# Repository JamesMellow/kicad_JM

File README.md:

# kicad_JM
Collection od different Kicad files including some:
-selfmade footprints
-projects
-gerber files

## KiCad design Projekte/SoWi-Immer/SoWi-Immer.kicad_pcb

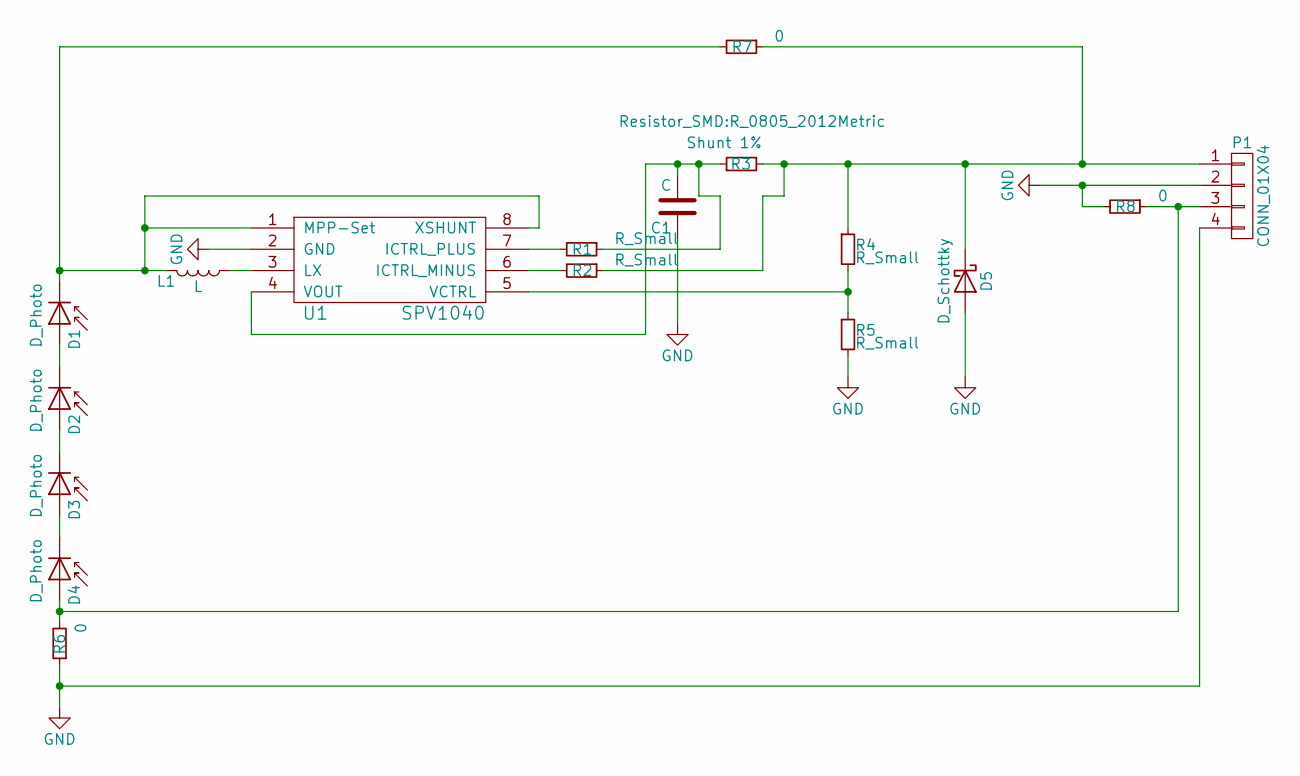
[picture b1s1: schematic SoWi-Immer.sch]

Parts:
C1: C; C_1206_3216Metric
D1, D2, D3, D4: D_Photo; KXOB22-12X1F
D5: D_Schottky; D_0805
L1: L; R_0815_2038Metric
P1: CONN_01X04; PinHeader_1x04_P1.27mm_Vertical
R1, R2, R4, R5: R_Small; R_0805_2012Metric
R3: Shunt 1%; R_0805_2012Metric
R6, R7, R8: 0; R_0805_2012Metric
U1: SPV1040; TSSOP-8_4.4x3mm_P0.65mm

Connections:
GND: C1.1, D5.2 (A), P1.2, P1.4, R5.2, R6.1, R8.2, U1.2 (GND)
unnamed: C1.2, R1.1, R3.1, U1.4 (VOUT)
unnamed: D1.1 (K), L1.2, R7.2, U1.1 (MPP-Set), U1.8 (XSHUNT)
unnamed: D1.2 (A), D2.1 (K)
unnamed: D2.2 (A), D3.1 (K)
unnamed: D3.2 (A), D4.1 (K)
unnamed: D4.2 (A), P1.3, R6.2, R8.1
unnamed: D5.1 (K), P1.1, R2.1, R3.2, R4.1, R7.1
unnamed: L1.1, U1.3 (LX)
unnamed: R1.2, U1.7 (ICTRL_PLUS)
unnamed: R2.2, U1.6 (ICTRL_MINUS)
unnamed: R4.2, R5.1, U1.5 (VCTRL)

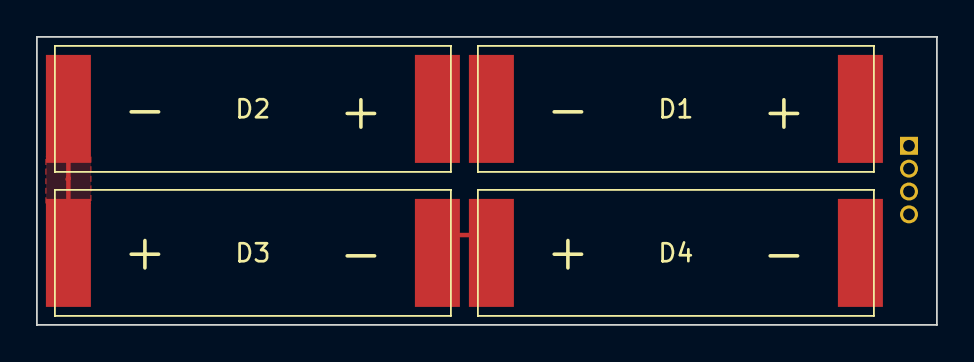
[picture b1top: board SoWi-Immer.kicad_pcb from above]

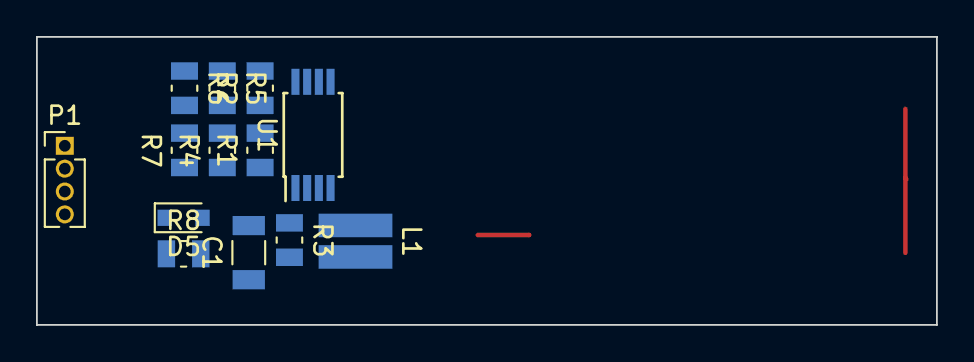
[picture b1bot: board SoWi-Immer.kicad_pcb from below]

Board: 2 copper layers, 50.0 x 16.0 mm, 17 parts (13 on the bottom side), 12 nets.

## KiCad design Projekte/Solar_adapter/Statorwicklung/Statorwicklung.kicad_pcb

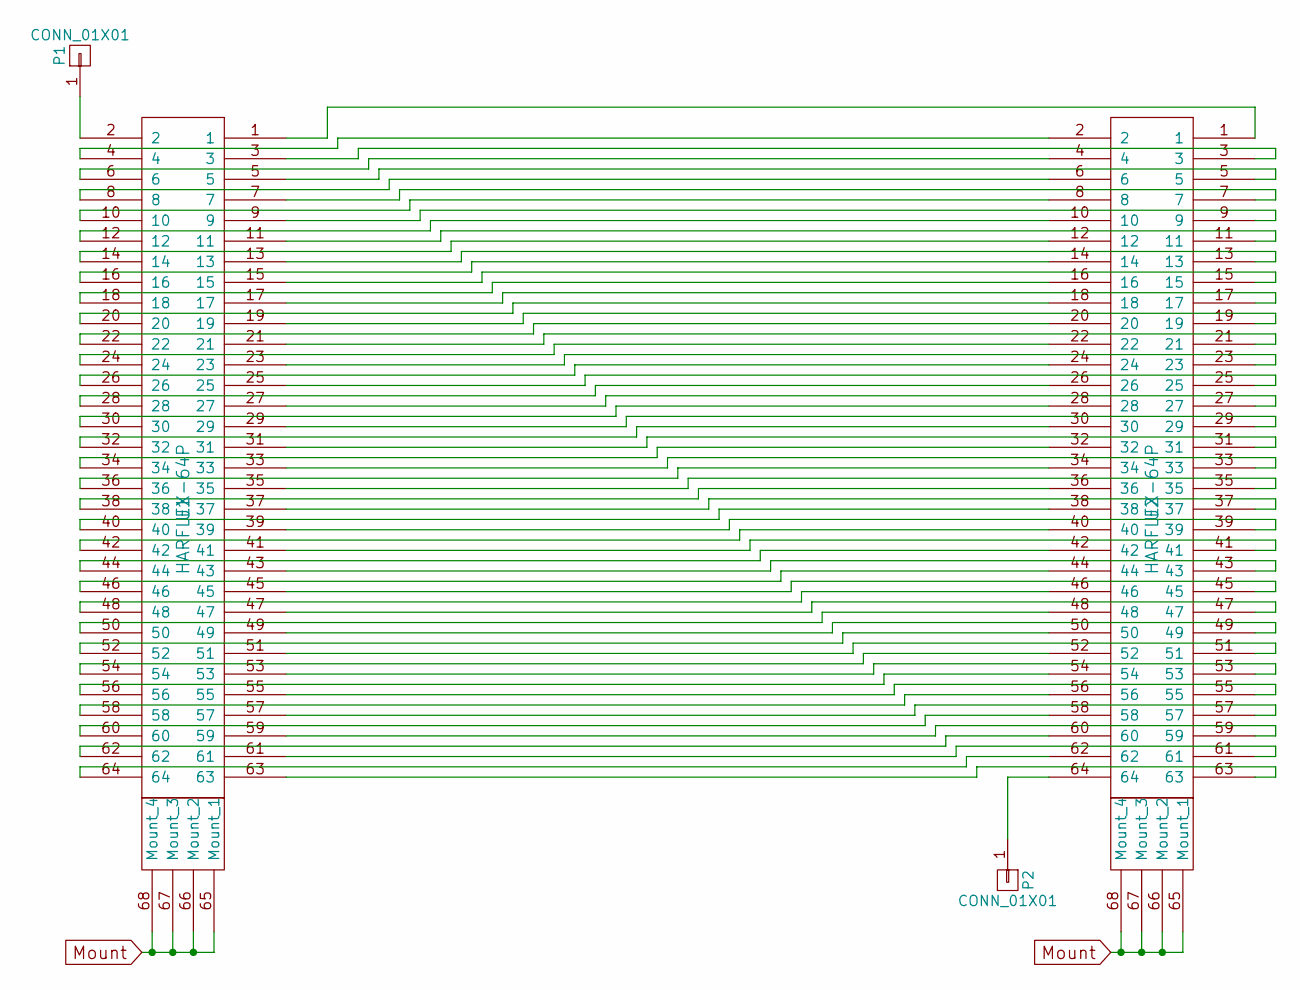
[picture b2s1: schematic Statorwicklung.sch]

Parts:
P1, P2: CONN_01X01; 1pin
U1, U2: HARFLEX-64P; Harting_64p_Stiftleiste

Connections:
Mount: U1.65 (Mount_1), U1.66 (Mount_2), U1.67 (Mount_3), U1.68 (Mount_4), U2.65 (Mount_1), U2.66 (Mount_2), U2.67 (Mount_3), U2.68 (Mount_4)
unnamed: P1.1, U1.2
unnamed: P2.1, U2.64
unnamed: U1.1, U2.1
unnamed: U1.3, U2.3
unnamed: U1.4, U2.2
unnamed: U1.5, U2.5
unnamed: U1.6, U2.4
unnamed: U1.7, U2.7
unnamed: U1.8, U2.6
unnamed: U1.9, U2.9
unnamed: U1.10, U2.8
unnamed: U1.11, U2.11
unnamed: U1.12, U2.10
unnamed: U1.13, U2.13
unnamed: U1.14, U2.12
unnamed: U1.15, U2.15
unnamed: U1.16, U2.14
unnamed: U1.17, U2.17
unnamed: U1.18, U2.16
unnamed: U1.19, U2.19
unnamed: U1.20, U2.18
unnamed: U1.21, U2.21
unnamed: U1.22, U2.20
unnamed: U1.23, U2.23
unnamed: U1.24, U2.22
unnamed: U1.25, U2.25
unnamed: U1.26, U2.24
unnamed: U1.27, U2.27
unnamed: U1.28, U2.26
unnamed: U1.29, U2.29
unnamed: U1.30, U2.28
unnamed: U1.31, U2.31
unnamed: U1.32, U2.30
unnamed: U1.33, U2.33
unnamed: U1.34, U2.32
unnamed: U1.35, U2.35
unnamed: U1.36, U2.34
unnamed: U1.37, U2.37
unnamed: U1.38, U2.36
unnamed: U1.39, U2.39
unnamed: U1.40, U2.38
unnamed: U1.41, U2.41
unnamed: U1.42, U2.40
unnamed: U1.43, U2.43
unnamed: U1.44, U2.42
unnamed: U1.45, U2.45
unnamed: U1.46, U2.44
unnamed: U1.47, U2.47
unnamed: U1.48, U2.46
unnamed: U1.49, U2.49
unnamed: U1.50, U2.48
unnamed: U1.51, U2.51
unnamed: U1.52, U2.50
unnamed: U1.53, U2.53
unnamed: U1.54, U2.52
unnamed: U1.55, U2.55
unnamed: U1.56, U2.54
unnamed: U1.57, U2.57
unnamed: U1.58, U2.56
unnamed: U1.59, U2.59
unnamed: U1.60, U2.58
unnamed: U1.61, U2.61
unnamed: U1.62, U2.60
unnamed: U1.63, U2.63
unnamed: U1.64, U2.62

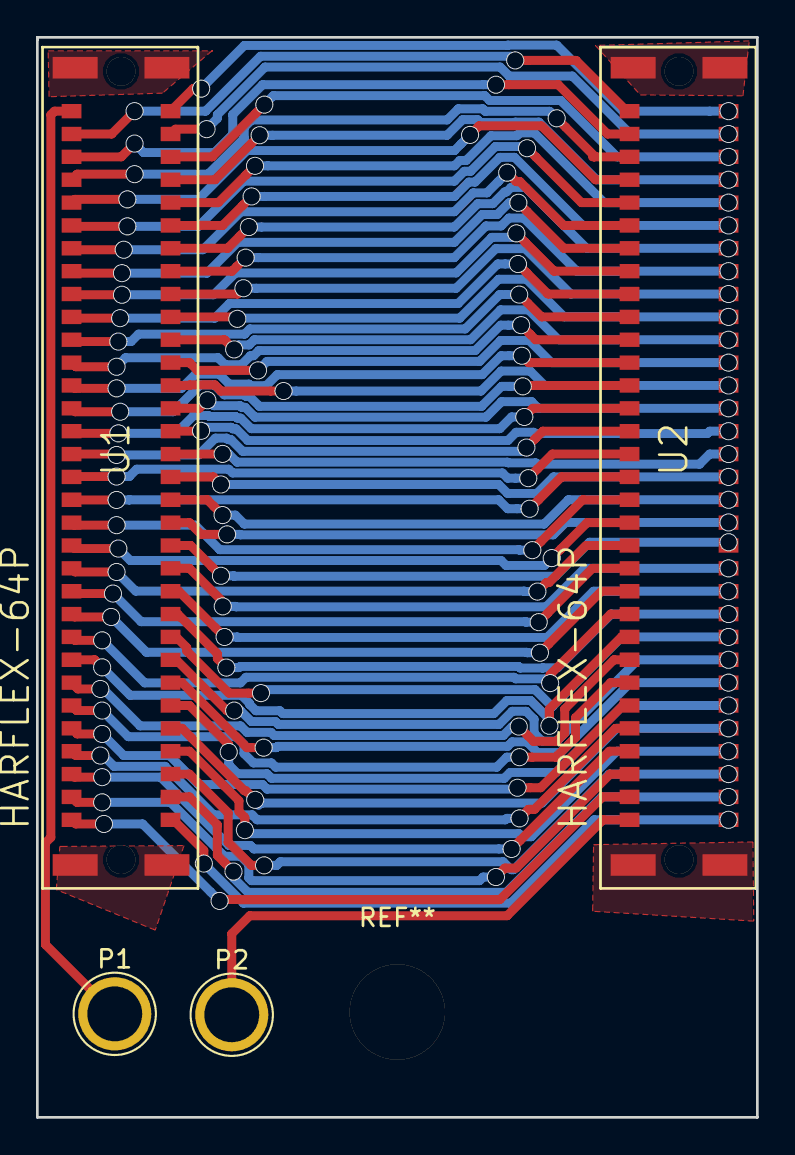
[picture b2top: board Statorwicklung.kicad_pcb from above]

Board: 2 copper layers, 40.0 x 60.0 mm, 4 parts (0 on the bottom side), 66 nets.

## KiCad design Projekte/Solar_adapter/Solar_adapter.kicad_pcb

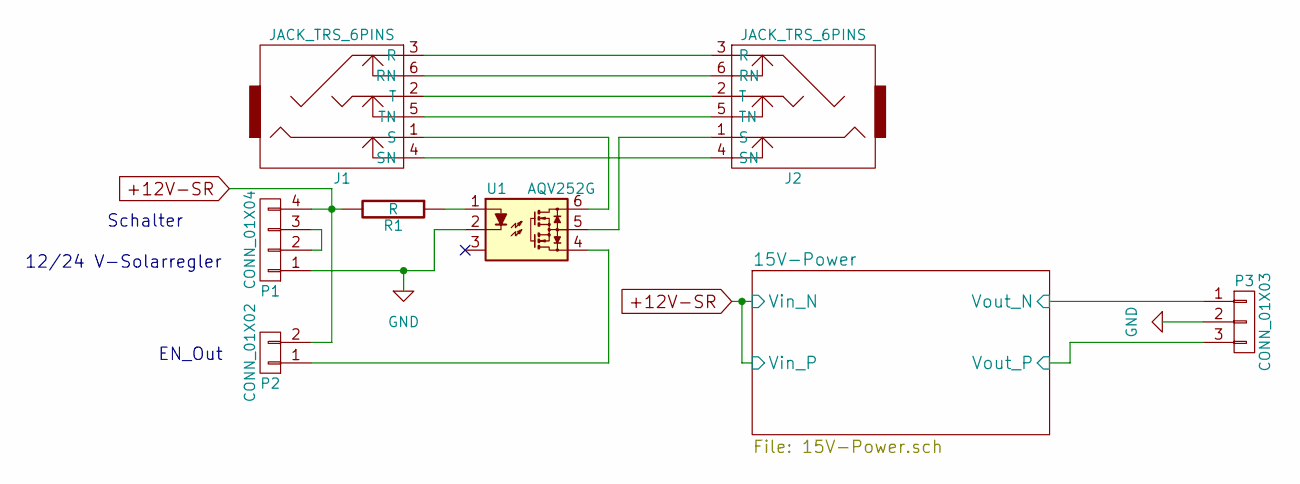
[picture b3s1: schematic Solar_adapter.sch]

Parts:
J1, J2: JACK_TRS_6PINS; RJ12_E
P1: CONN_01X04; WAGO_734_4pin_Straight
P2: CONN_01X02; WAGO_734_2pin_Straight
P3: CONN_01X03; WAGO_734_3pin_Straight
R1: R; R_0805_HandSoldering
U1: AQV252G; DIP-6_W7.62mm

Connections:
+12V-SR: P1.4, P2.2, R1.2; also elsewhere on the board
GND: P1.1, P3.2, U1.2; also elsewhere on the board
unnamed: J1.1 (S), U1.6
unnamed: J1.2 (T), J2.2 (T)
unnamed: J1.3 (R), J2.3 (R)
unnamed: J1.4 (SN), J2.4 (SN)
unnamed: J1.5 (TN), J2.5 (TN)
unnamed: J1.6 (RN), J2.6 (RN)
unnamed: J2.1 (S), U1.5
unnamed: P1.2, P1.3
unnamed: P2.1, U1.4
unnamed: R1.1, U1.1
OUT_N: P3.1; also elsewhere on the board
OUT_P: P3.3; also elsewhere on the board

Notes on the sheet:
Schalter
12/24 V-Solarregler
EN_Out

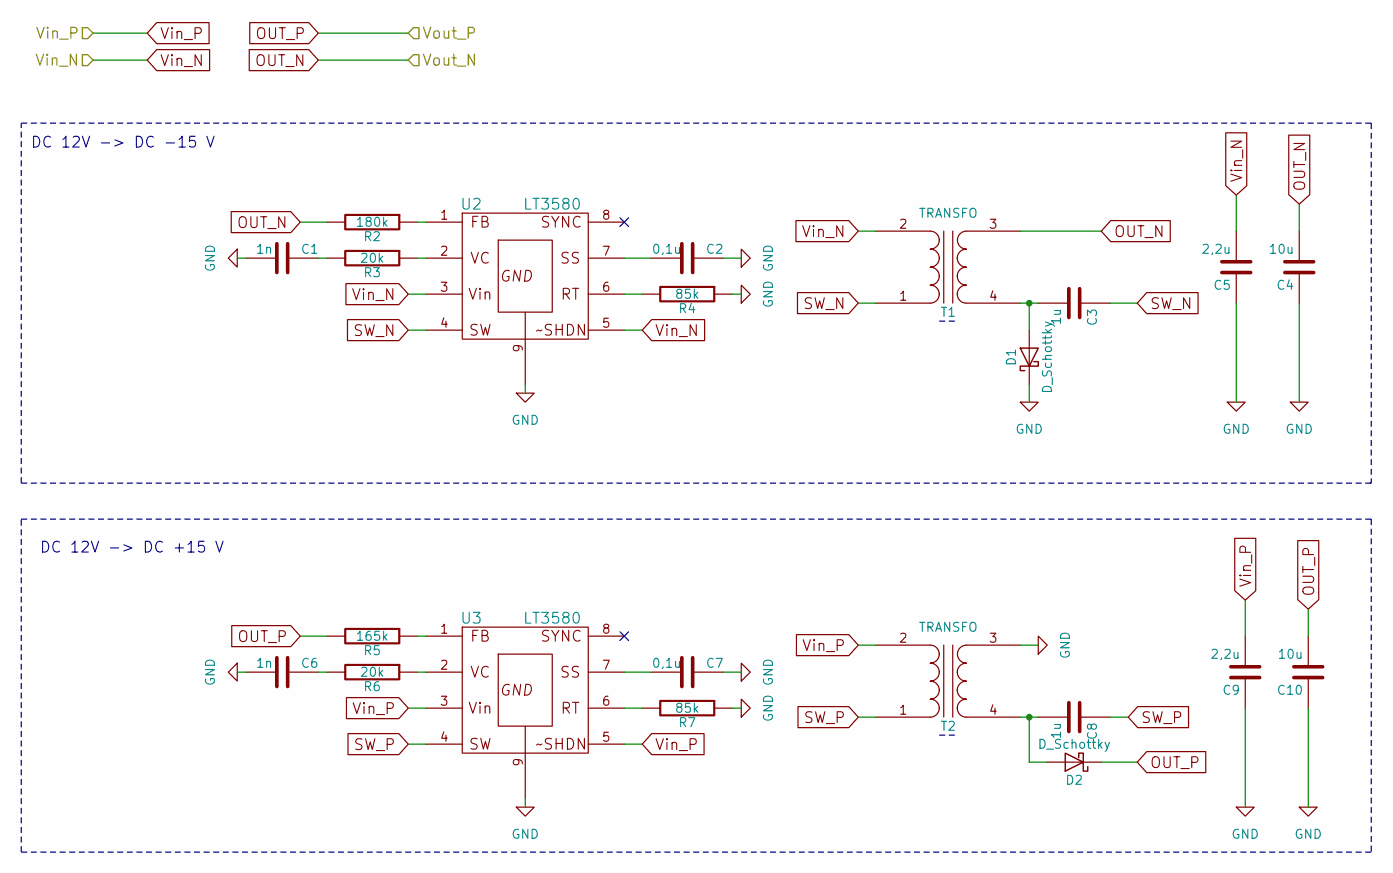
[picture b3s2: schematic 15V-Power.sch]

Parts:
C1, C6: 1n; C_0805_HandSoldering
C2, C7: 0,1u; C_0805_HandSoldering
C3, C8: 1u; C_1206_HandSoldering
C4, C10: 10u; C_0805_HandSoldering
C5, C9: 2,2u; C_0805_HandSoldering
D1, D2: D_Schottky; MELF_Standard
R2: 180k; R_0805_HandSoldering
R3, R6: 20k; R_0805_HandSoldering
R4, R7: 85k; R_0805_HandSoldering
R5: 165k; R_0805_HandSoldering
T1, T2: TRANSFO; 744878002_WE
U2, U3: LT3580; MSOP-8-1EP_3x3mm_Pitch0.65mm

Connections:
+12V-SR: C5.2, C9.2, T1.2 (AB), T2.2 (AB), U2.3, U2.5, U3.3, U3.5; also elsewhere on the board
GND: C1.2, C2.1, C4.1, C5.1, C6.2, C7.1, C9.1, C10.1, D1.1 (K), R4.1, R7.1, T2.3 (SA), U2.9, U3.9; also elsewhere on the board
unnamed: C1.1, R3.2
unnamed: C2.2, U2.7
unnamed: C3.2, D1.2 (A), T1.4 (SB)
unnamed: C6.1, R6.2
unnamed: C7.2, U3.7
unnamed: C8.2, D2.2 (A), T2.4 (SB)
unnamed: R2.1, U2.1
unnamed: R3.1, U2.2
unnamed: R4.2, U2.6
unnamed: R5.1, U3.1
unnamed: R6.1, U3.2
unnamed: R7.2, U3.6
OUT_N: C4.2, R2.2, T1.3 (SA); also elsewhere on the board
OUT_P: C10.2, D2.1 (K), R5.2; also elsewhere on the board
SW_N: C3.1, T1.1 (AA), U2.4
SW_P: C8.1, T2.1 (AA), U3.4

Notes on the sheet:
DC 12V -> DC -15 V
DC 12V -> DC +15 V

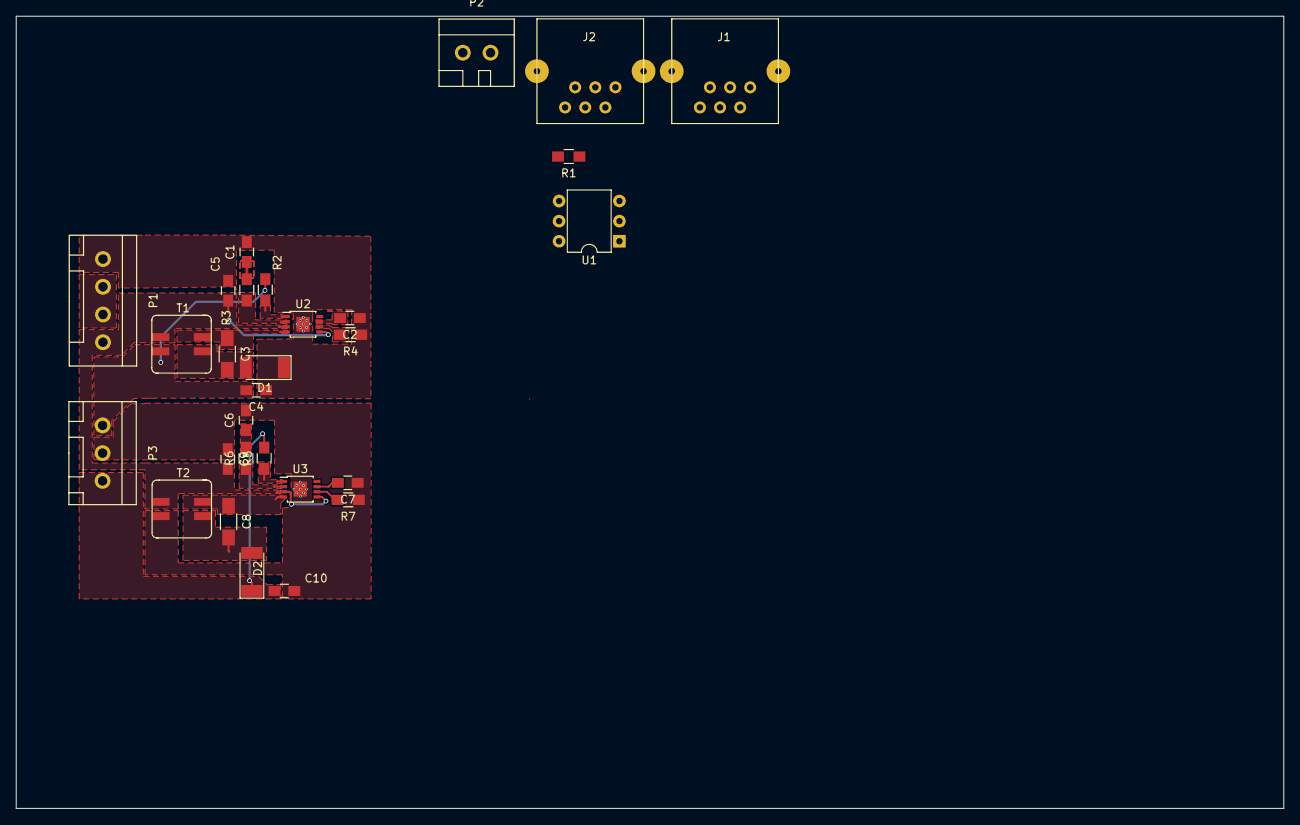
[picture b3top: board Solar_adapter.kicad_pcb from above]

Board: 2 copper layers, 160.0 x 100.0 mm, 29 parts (0 on the bottom side), 28 nets.

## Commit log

2017-12-17 Readme hinzugefuegt
2017-12-17 Prejekt SOWI-Immer hinzugefügt
2017-12-17 Diverse Projekte hinzugefügt
2017-12-17 Diverse Bibliotheksdateien angehängt... Neue Ordner angelegt
2017-12-17 3d-Shapes-Ordner und Solarzellen.STP hinzugefügt
2017-12-17 test hinzugefügt
2017-12-17 Diverse Dateien hinzugefügt
2017-12-17 Gerberdaten Adapterplatine hinzugefügt & Fp-lib-table hinzugefügt
2017-12-17 Eigene Schemativ-Libraries eingefügt
2017-12-18 Schematic & PCB geändert
2017-12-20 Kléine Laxoutanpassung
